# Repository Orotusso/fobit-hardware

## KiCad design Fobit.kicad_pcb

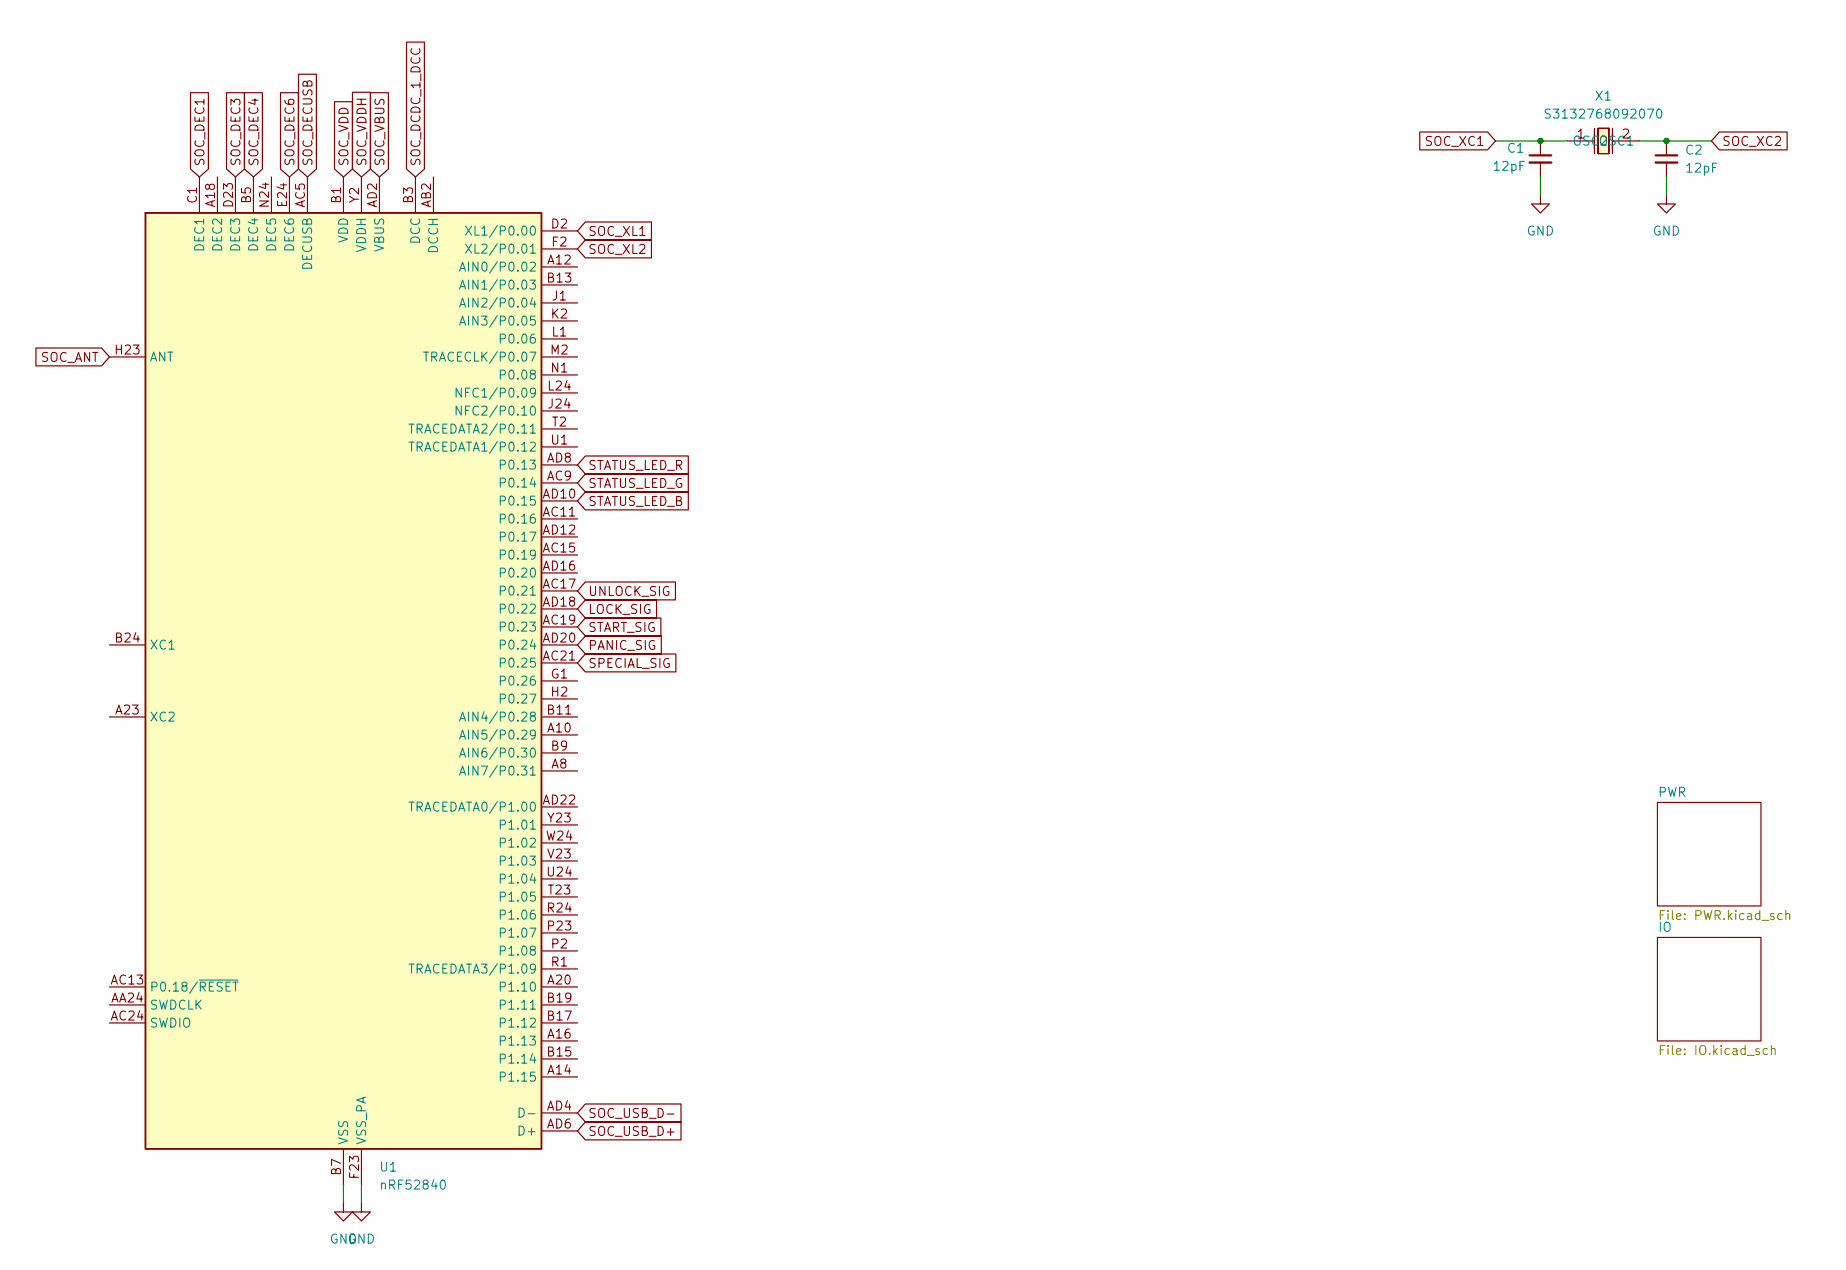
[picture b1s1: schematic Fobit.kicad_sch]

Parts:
C1, C2: 12pF; C_0402_1005Metric_Pad0.74x0.62mm_HandSolder
U1: nRF52840; Nordic_AQFN-73-1EP_7x7mm_P0.5mm
X1: S3132768092070; OSC-SMD_2P-L3.2-W1.5; MPN S3132768092070; LCSC Part C479190

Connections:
BAT_-: C1.2, C2.2, U1.B7 (VSS), U1.EP (VSS), U1.F23 (VSS_PA); also elsewhere on the board
LOCK_SIG: U1.AD18 (P0.22); also elsewhere on the board
PANIC_SIG: U1.AD20 (P0.24); also elsewhere on the board
SOC_ANT: U1.H23 (ANT)
SOC_DCDC_1_DCC: U1.B3 (DCC); also elsewhere on the board
SOC_DEC1: U1.C1 (DEC1); also elsewhere on the board
SOC_DEC3: U1.D23 (DEC3); also elsewhere on the board
SOC_DEC4: U1.B5 (DEC4), U1.E24 (DEC6); also elsewhere on the board
SOC_DECUSB: U1.AC5 (DECUSB); also elsewhere on the board
SOC_USB_D+: U1.AD6 (D+); also elsewhere on the board
SOC_USB_D-: U1.AD4 (D-); also elsewhere on the board
SOC_VBUS: U1.A22 (VDD), U1.AD2 (VBUS), U1.AD14 (VDD), U1.AD23 (VDD), U1.B1 (VDD), U1.W1 (VDD), U1.Y2 (VDDH); also elsewhere on the board
SOC_XC1: C1.1, X1.1 (OSC1)
SOC_XC2: C2.1, X1.2 (OSC2)
SOC_XL1: U1.D2 (XL1/P0.00)
SOC_XL2: U1.F2 (XL2/P0.01)
SPECIAL_SIG: U1.AC21 (P0.25); also elsewhere on the board
START_SIG: U1.AC19 (P0.23); also elsewhere on the board
STATUS_LED_B: U1.AD10 (P0.15); also elsewhere on the board
STATUS_LED_G: U1.AC9 (P0.14); also elsewhere on the board
STATUS_LED_R: U1.AD8 (P0.13); also elsewhere on the board
UNLOCK_SIG: U1.AC17 (P0.21); also elsewhere on the board

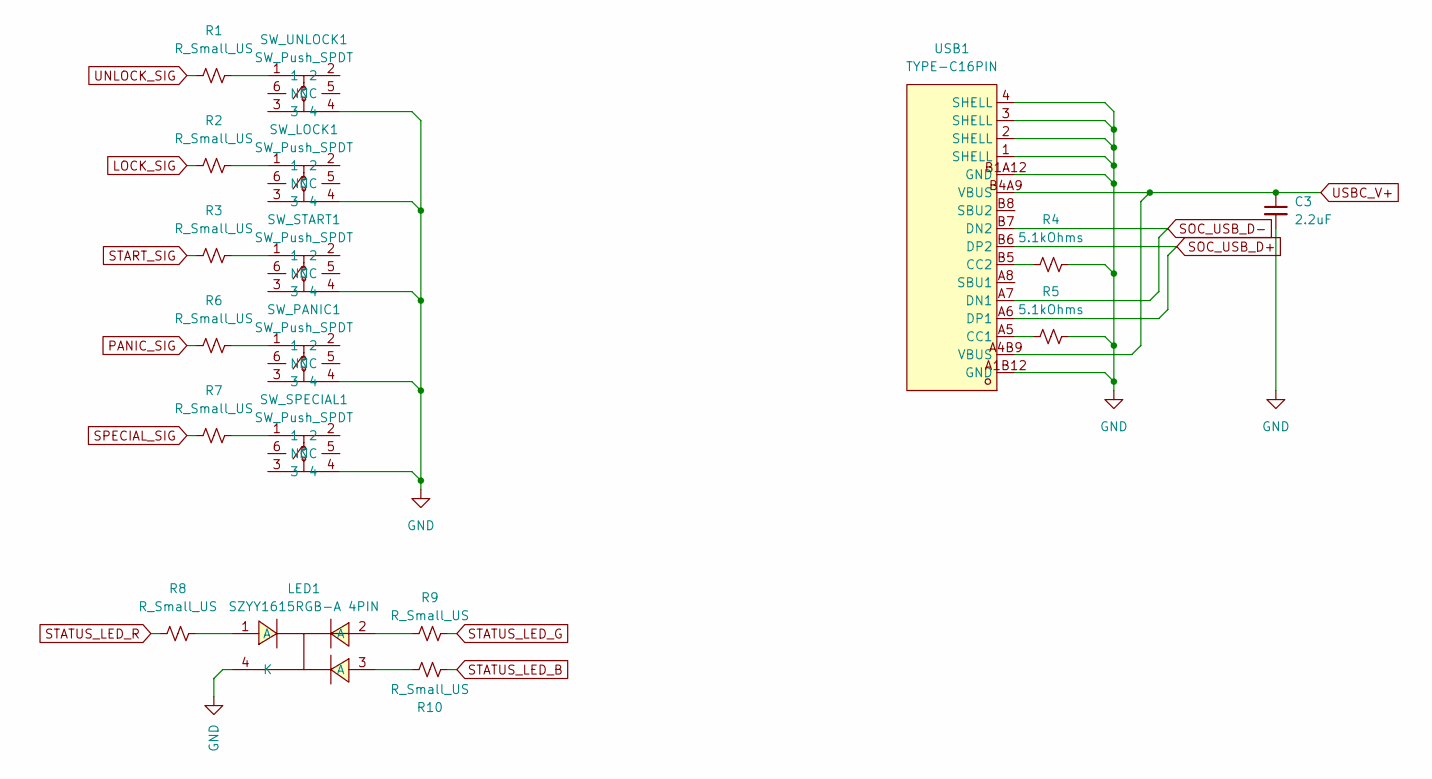
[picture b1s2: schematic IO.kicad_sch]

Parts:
C3: 2.2uF; C_0402_1005Metric_Pad0.74x0.62mm_HandSolder
LED1: SZYY1615RGB-A 4PIN; LED-ARRAY-SMD_4P-L1.6-W1.5_SZYY1615RGB-A; MPN SZYY1615RGB-A 4pin; LCSC Part C3029072
R1, R2, R3, R6, R7, R8, R9, R10: R_Small_US; R_0402_1005Metric_Pad0.72x0.64mm_HandSolder
R4, R5: 5.1kOhms; R_0402_1005Metric_Pad0.72x0.64mm_HandSolder
SW_LOCK1: SW_Push_SPDT; SW-SMD_4P-L5.2-W5.2-P3.70-LS6.4_UK-B0233XX; MPN G4R152312; LCSC Part C49393646
SW_PANIC1: SW_Push_SPDT; SW-SMD_4P-L5.2-W5.2-P3.70-LS6.4_UK-B0233XX; MPN G4R152312; LCSC Part C49393646
SW_SPECIAL1: SW_Push_SPDT; SW-SMD_4P-L5.2-W5.2-P3.70-LS6.4_UK-B0233XX; MPN G4R152312; LCSC Part C49393646
SW_START1: SW_Push_SPDT; SW-SMD_4P-L5.2-W5.2-P3.70-LS6.4_UK-B0233XX; MPN G4R152312; LCSC Part C49393646
SW_UNLOCK1: SW_Push_SPDT; SW-SMD_4P-L5.2-W5.2-P3.70-LS6.4_UK-B0233XX; MPN G4R152312; LCSC Part C49393646
USB1: TYPE-C16PIN; USB-C-SMD_TYPE-C16PIN; MPN TYPE-C16PIN; LCSC Part C393939

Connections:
BAT_-: C3.2, LED1.4 (K), R4.1, R5.1, SW_LOCK1.4, SW_PANIC1.4, SW_SPECIAL1.4, SW_START1.4, SW_UNLOCK1.4, USB1.1 (SHELL), USB1.2 (SHELL), USB1.3 (SHELL), USB1.4 (SHELL), USB1.A1B12 (GND), USB1.B1A12 (GND); also elsewhere on the board
LOCK_SIG: R2.1; also elsewhere on the board
unnamed: LED1.1 (A), R8.2
unnamed: LED1.2 (A), R9.2
unnamed: LED1.3 (A), R10.2
unnamed: R1.2, SW_UNLOCK1.1
unnamed: R2.2, SW_LOCK1.1
unnamed: R3.2, SW_START1.1
unnamed: R6.2, SW_PANIC1.1
unnamed: R7.2, SW_SPECIAL1.1
unnamed: R5.2, USB1.A5 (CC1)
unnamed: R4.2, USB1.B5 (CC2)
PANIC_SIG: R6.1; also elsewhere on the board
SOC_USB_D+: USB1.A6 (DP1), USB1.B6 (DP2); also elsewhere on the board
SOC_USB_D-: USB1.A7 (DN1), USB1.B7 (DN2); also elsewhere on the board
SPECIAL_SIG: R7.1; also elsewhere on the board
START_SIG: R3.1; also elsewhere on the board
STATUS_LED_B: R10.1; also elsewhere on the board
STATUS_LED_G: R9.1; also elsewhere on the board
STATUS_LED_R: R8.1; also elsewhere on the board
UNLOCK_SIG: R1.1; also elsewhere on the board
USBC_V+: C3.1, USB1.A4B9 (VBUS), USB1.B4A9 (VBUS); also elsewhere on the board

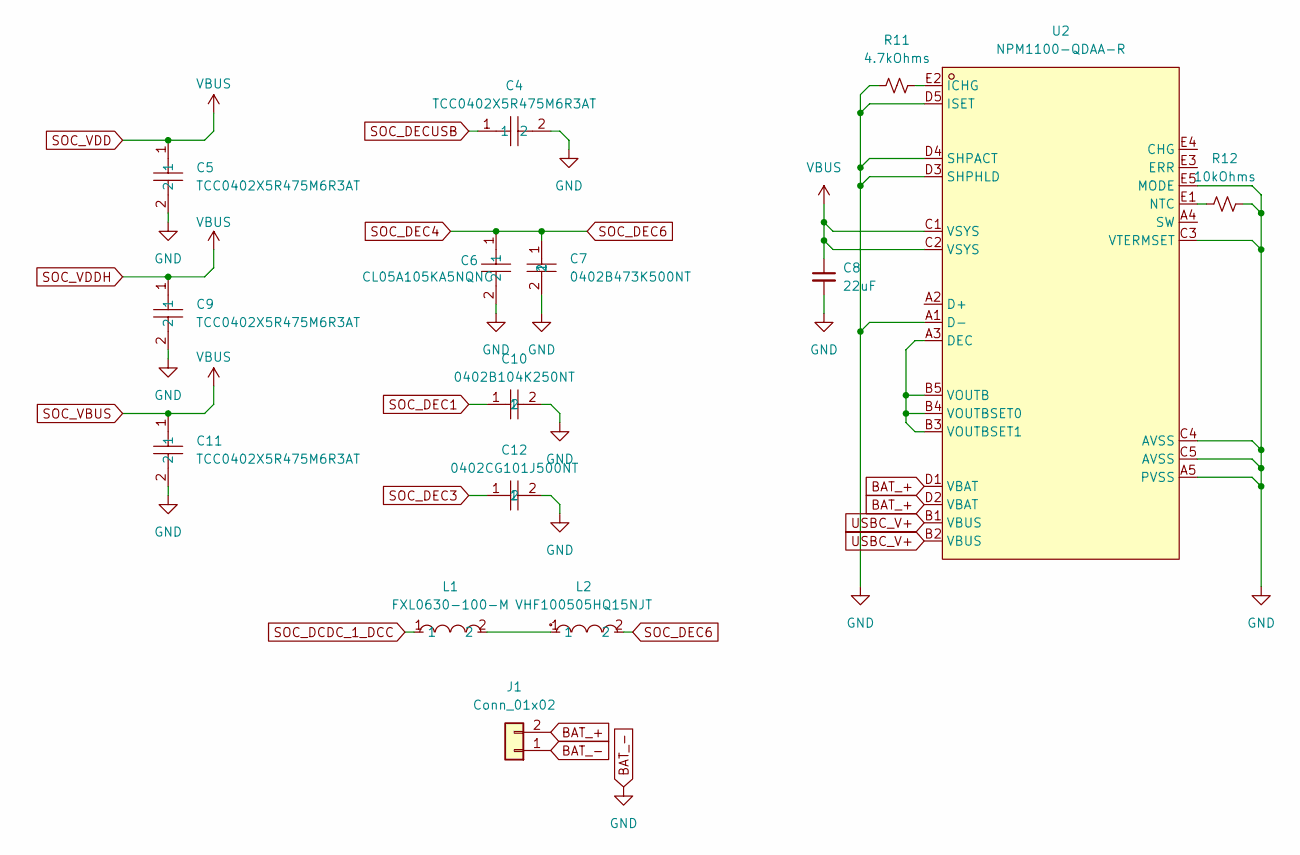
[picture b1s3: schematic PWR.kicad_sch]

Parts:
C4, C5, C9, C11: TCC0402X5R475M6R3AT; C0402; MPN TCC0402X5R475M6R3AT; LCSC Part C380302
C6: CL05A105KA5NQNC; C0402; MPN CL05A105KA5NQNC; LCSC Part C52923
C7: 0402B473K500NT; C0402; MPN 0402B473K500NT; LCSC Part C82219
C8: 22uF; C_0402_1005Metric_Pad0.74x0.62mm_HandSolder
C10: 0402B104K250NT; C0402; MPN 0402B104K250NT; LCSC Part C56392
C12: 0402CG101J500NT; C0402; MPN 0402CG101J500NT; LCSC Part C1546
J1: Conn_01x02; JST_PH_S2B-PH-K_1x02_P2.00mm_Horizontal
L1: FXL0630-100-M; IND-SMD_L7.3-W6.8; MPN FXL0630-100-M; LCSC Part C167223
L2: VHF100505HQ15NJT; L0402-R-RD; MPN VHF100505HQ15NJT; LCSC Part C395049
R11: 4.7kOhms; R_0402_1005Metric_Pad0.72x0.64mm_HandSolder
R12: 10kOhms; R_0402_1005Metric_Pad0.72x0.64mm_HandSolder
U2: NPM1100-QDAA-R; WLCSP-25_L2.1-W2.1-R5-C5-P0.40-TL-1; LCSC Part C5240943

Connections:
BAT_+: J1.2, U2.D1 (VBAT), U2.D2 (VBAT)
BAT_-: C4.2, C5.2, C6.2, C7.2, C8.2, C9.2, C10.2, C11.2, C12.2, J1.1, R11.1, R12.2, U2.A1 (D-), U2.A5 (PVSS), U2.C3 (VTERMSET), U2.C4 (AVSS), U2.C5 (AVSS), U2.D3 (SHPHLD), U2.D4 (SHPACT), U2.D5 (ISET), U2.E5 (MODE); also elsewhere on the board
unnamed: L1.2, L2.1
unnamed: U2.A3 (DEC), U2.B3 (VOUTBSET1), U2.B4 (VOUTBSET0), U2.B5 (VOUTB)
unnamed: R11.2, U2.E2 (ICHG)
unnamed: R12.1, U2.E1 (NTC)
SOC_DCDC_1_DCC: L1.1; also elsewhere on the board
SOC_DEC1: C10.1; also elsewhere on the board
SOC_DEC3: C12.1; also elsewhere on the board
SOC_DEC4: C6.1, C7.1, L2.2; also elsewhere on the board
SOC_DECUSB: C4.1; also elsewhere on the board
SOC_VBUS: C5.1, C8.1, C9.1, C11.1, U2.C1 (VSYS), U2.C2 (VSYS); also elsewhere on the board
USBC_V+: U2.B1 (VBUS), U2.B2 (VBUS); also elsewhere on the board

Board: 2 copper layers, 37 parts (0 on the bottom side), 35 nets, no tracks yet.
